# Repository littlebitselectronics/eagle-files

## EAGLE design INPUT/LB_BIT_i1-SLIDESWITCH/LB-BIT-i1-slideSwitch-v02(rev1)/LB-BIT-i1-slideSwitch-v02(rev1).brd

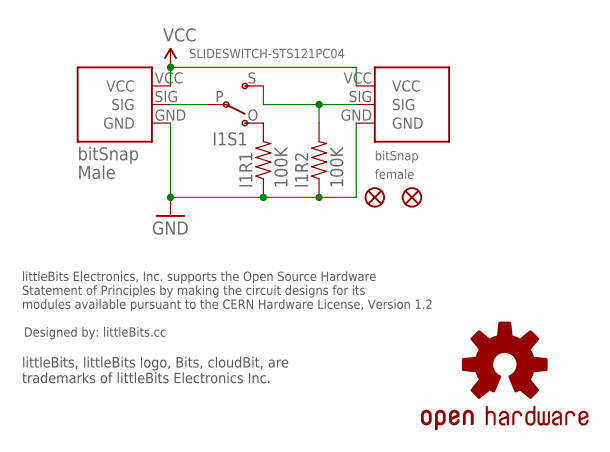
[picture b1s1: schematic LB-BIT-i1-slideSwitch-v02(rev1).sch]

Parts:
I1BSF: BITSNAP_FEMALE
I1BSM: BITSNAP_MALE
I1FD1, I1FD2: FIDUCIAL1X2; FIDUCIAL-1X2
I1R1, I1R2: 100K; 0603-RES
I1S1: SLIDESWITCH-STS121PC04
U$1: OSHWCREDIT
U$2: OSHW-LOGOS; OSHW-LOGO-S

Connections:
GND: I1BSF.GND, I1BSM.GND, I1R1.1, I1R2.1
unnamed: I1BSF.SIG, I1R2.2, I1S1.S
unnamed: I1BSM.SIG, I1S1.P
unnamed: I1R1.2, I1S1.O
VCC: I1BSF.VCC, I1BSM.VCC

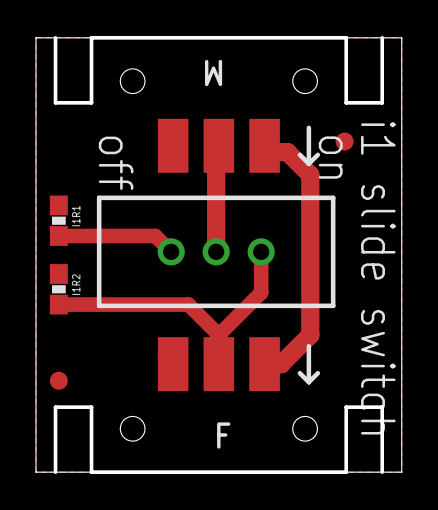
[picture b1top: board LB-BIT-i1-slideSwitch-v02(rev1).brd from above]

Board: 2 copper layers, 20.3 x 24.1 mm, 10 parts (0 on the bottom side), 5 nets.

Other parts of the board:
U$6: OSHW_FILLX150_NOTEXT

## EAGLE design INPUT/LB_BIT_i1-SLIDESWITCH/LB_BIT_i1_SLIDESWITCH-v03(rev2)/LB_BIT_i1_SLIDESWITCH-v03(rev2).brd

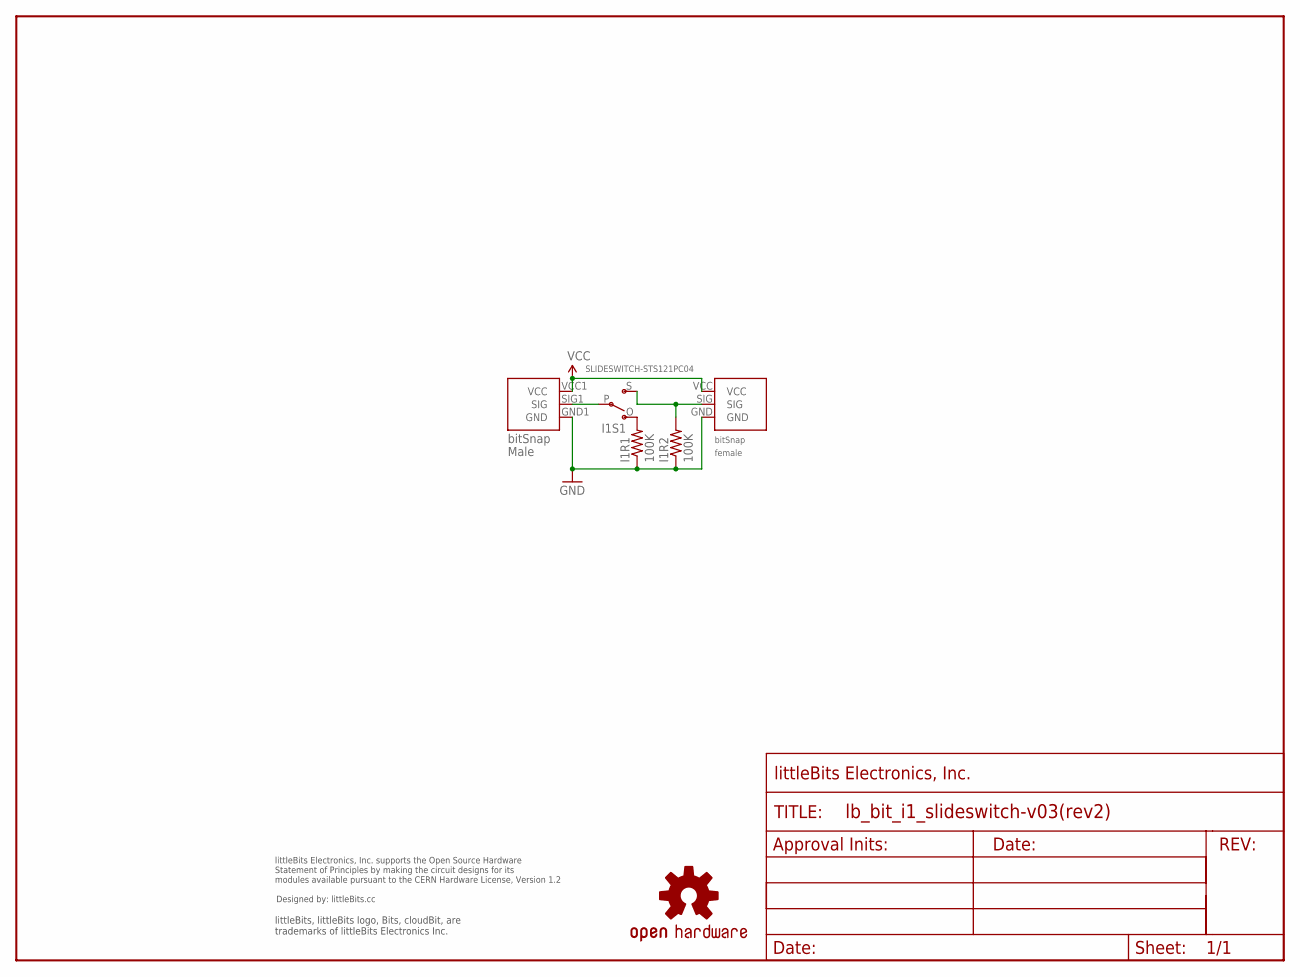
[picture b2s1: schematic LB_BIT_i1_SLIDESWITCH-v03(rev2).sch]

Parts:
I1BSF1: BITSNAP_V03_FEMALE
I1BSM1: BITSNAP_V03_MALE
I1R1, I1R2: 100K; 0603-RES
I1S1: SLIDESWITCH-STS121PC04
U$1: OSHW-LOGOL; OSHW-LOGO-L
U$2: FRAME-LETTER-OHWOHW; FABDWG01-OHW
U$3: LB_CREDITS; OSHWCREDIT

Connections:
GND: I1BSF1.GND, I1BSM1.GND1 (GND), I1R1.1, I1R2.1
unnamed: I1BSF1.SIG, I1R2.2, I1S1.S
unnamed: I1BSM1.SIG1 (SIG), I1S1.P
unnamed: I1R1.2, I1S1.O
VCC: I1BSF1.VCC, I1BSM1.VCC1 (VCC)

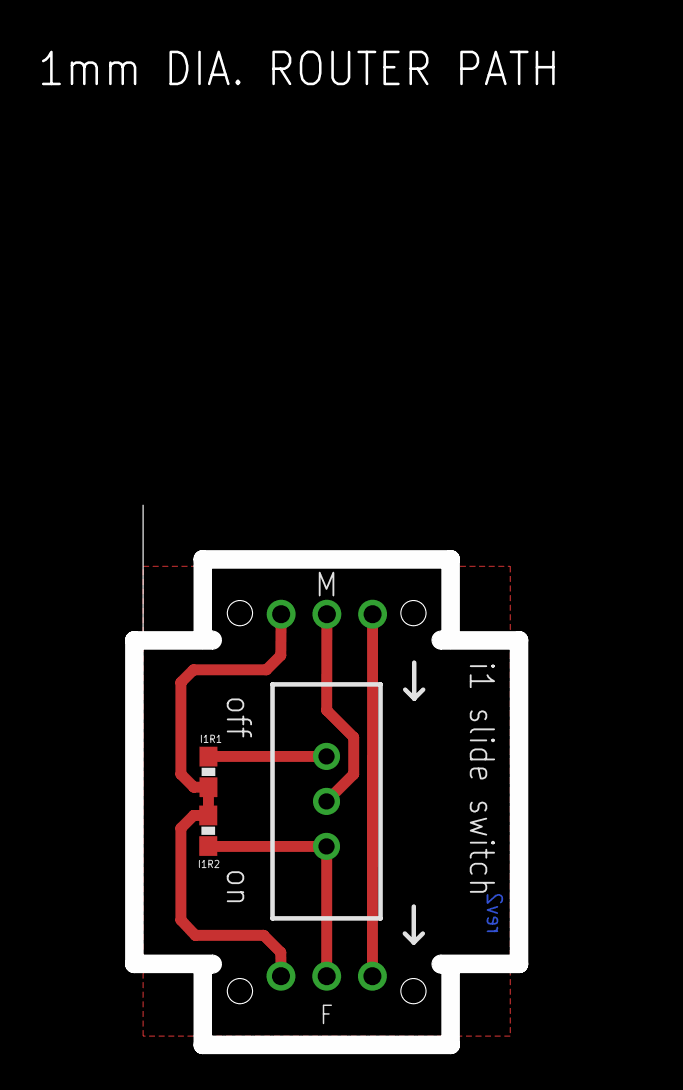
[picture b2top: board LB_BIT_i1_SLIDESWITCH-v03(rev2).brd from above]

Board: 2 copper layers, 21.4 x 27.0 mm, 9 parts (0 on the bottom side), 5 nets.

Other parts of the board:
U$6: OSHW_FILLX150_NOTEXT

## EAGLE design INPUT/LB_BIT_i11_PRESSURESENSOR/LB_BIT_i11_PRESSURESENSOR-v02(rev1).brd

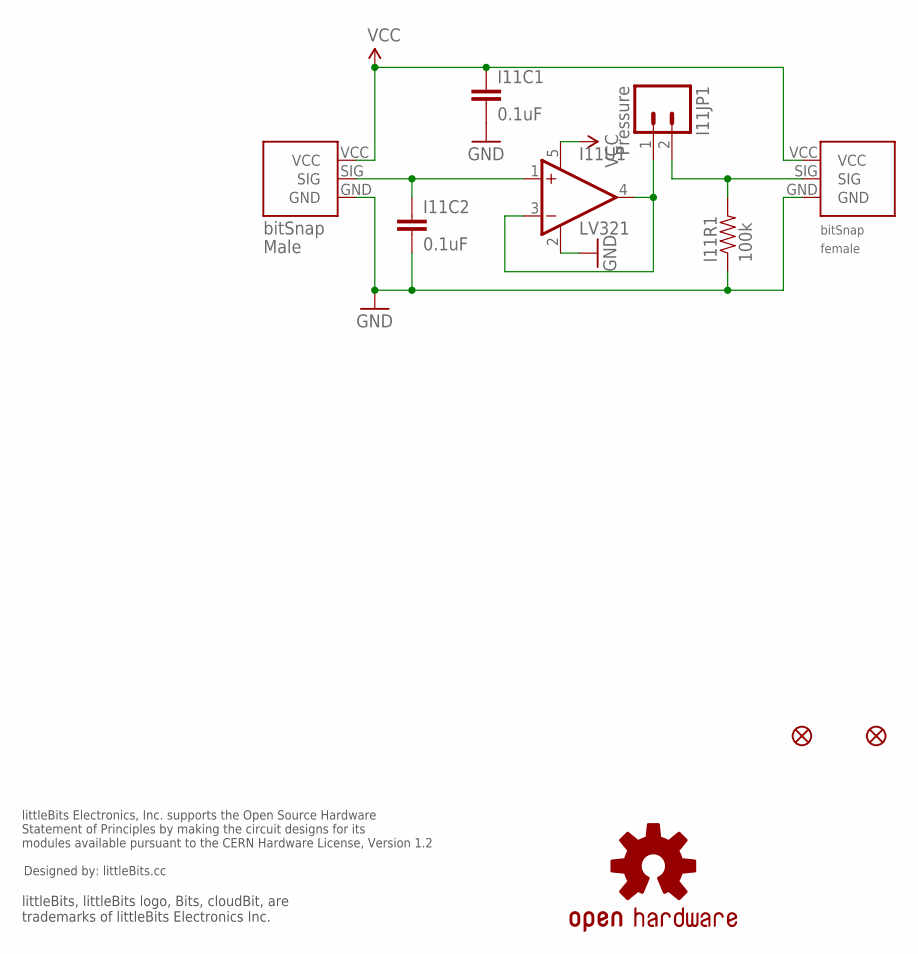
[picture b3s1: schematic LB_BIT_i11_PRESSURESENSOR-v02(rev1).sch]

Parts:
I11BSF: BITSNAP_FEMALE
I11BSM: BITSNAP_MALE
I11C1, I11C2: 0.1uF; 0603-CAP
I11JP1: Pressure; 1X02
I11R1: 100k; 0603-RES
I11U1: LV321; SC70-5
JP2, JP3: FIDUCIAL1X2.5; FIDUCIAL-1X2.5
U$1: OSHWCREDIT
U$4: OSHW-LOGOL; OSHW-LOGO-L

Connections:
GND: I11BSF.GND, I11BSM.GND, I11C1.2, I11C2.2, I11R1.1, I11U1.2 (V-)
unnamed: I11JP1.1, I11U1.3 (-IN), I11U1.4 (OUT)
PS: I11BSF.SIG, I11JP1.2, I11R1.2
SIG: I11BSM.SIG, I11C2.1, I11U1.1 (+IN)
VCC: I11BSF.VCC, I11BSM.VCC, I11C1.1, I11U1.5 (V+)

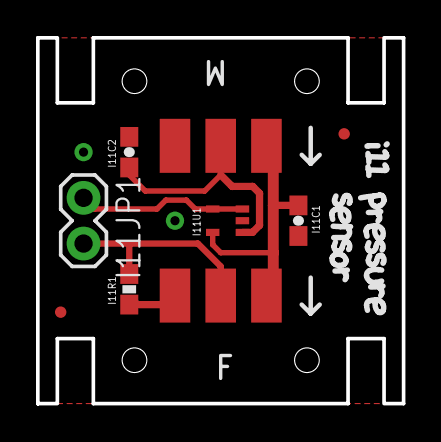
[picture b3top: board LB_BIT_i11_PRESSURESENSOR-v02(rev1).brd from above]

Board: 2 copper layers, 20.3 x 20.3 mm, 12 parts (0 on the bottom side), 5 nets.

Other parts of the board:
U$6: OSHW_FILLX150_NOTEXT

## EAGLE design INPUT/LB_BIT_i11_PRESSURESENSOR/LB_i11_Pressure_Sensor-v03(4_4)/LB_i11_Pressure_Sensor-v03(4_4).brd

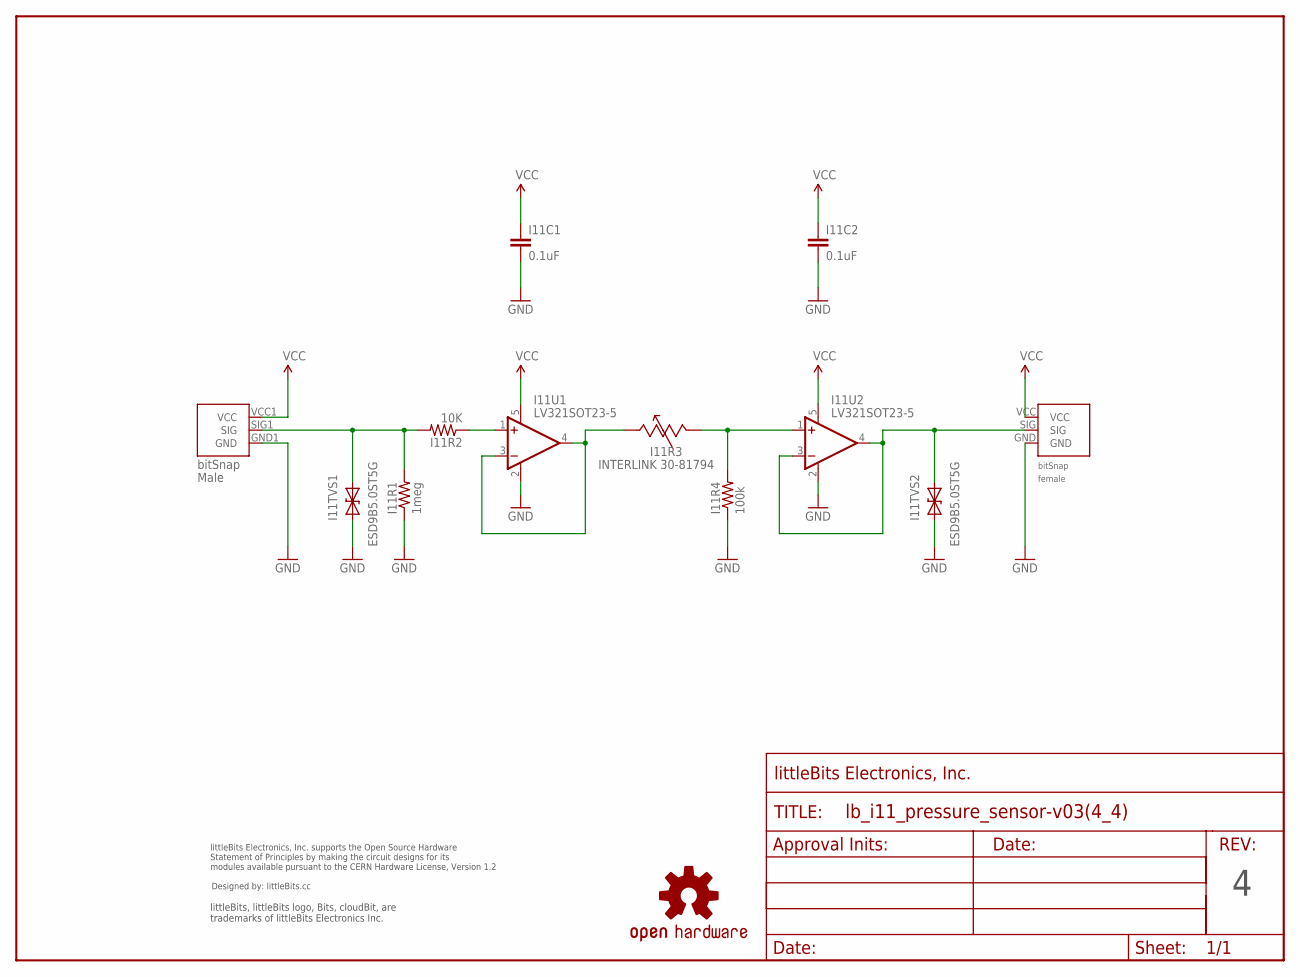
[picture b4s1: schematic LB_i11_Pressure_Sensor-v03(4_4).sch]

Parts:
FRAME1: FRAME-LETTER-OHWOHW; FABDWG01-OHW
I11BSF1: BITSNAP_V03_FEMALE
I11BSM1: BITSNAP_V03_MALE
I11C1, I11C2: 0.1uF; 0603-CAP
I11R1: 1meg; RES-0603
I11R2: 10K; RES-0603
I11R3: INTERLINK 30-81794; FSR-SMD
I11R4: 100k; 0603-RES
I11TVS1, I11TVS2: ESD9B5.0ST5G; SOD-923
I11U1, I11U2: LV321SOT23-5; SOT23-5
U$1: OSHW-LOGOL; OSHW-LOGO-L
U$7: LB_CREDITS; OSHWCREDIT

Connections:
GND: I11BSF1.GND, I11BSM1.GND1 (GND), I11C1.2, I11C2.2, I11R1.1, I11R4.1, I11TVS1.1 (A), I11TVS2.1 (A), I11U1.2 (V-), I11U2.2 (V-)
unnamed: I11R3.2 (A), I11R4.2, I11U2.1 (+IN)
unnamed: I11BSF1.SIG, I11TVS2.2 (C), I11U2.3 (-IN), I11U2.4 (OUT)
unnamed: I11R3.1, I11U1.3 (-IN), I11U1.4 (OUT)
unnamed: I11R2.1, I11U1.1 (+IN)
SIG2: I11BSM1.SIG1 (SIG), I11R1.2, I11R2.2, I11TVS1.2 (C)
VCC: I11BSF1.VCC, I11BSM1.VCC1 (VCC), I11C1.1, I11C2.1, I11U1.5 (V+), I11U2.5 (V+)

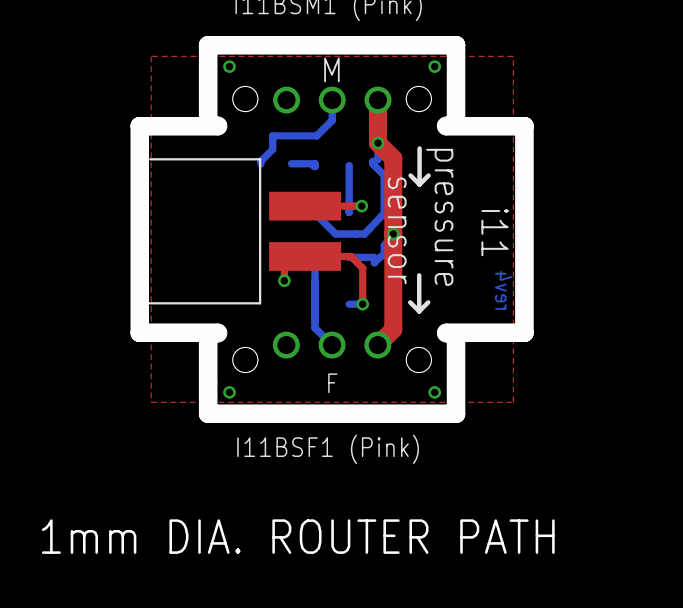
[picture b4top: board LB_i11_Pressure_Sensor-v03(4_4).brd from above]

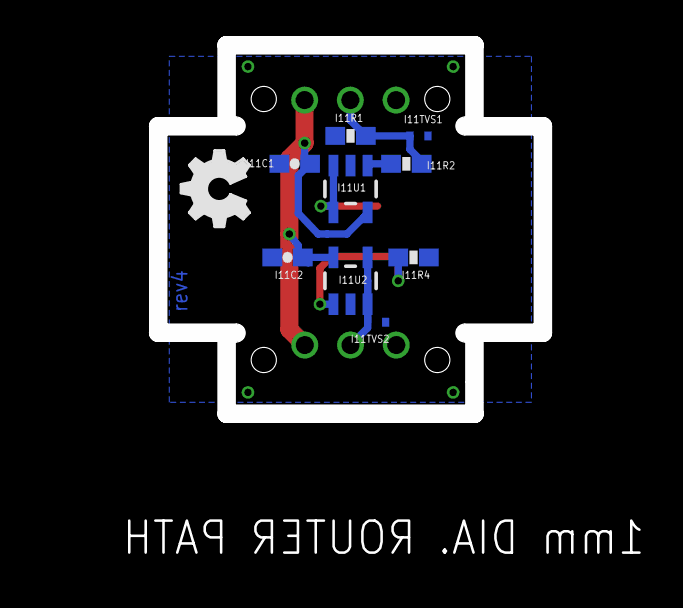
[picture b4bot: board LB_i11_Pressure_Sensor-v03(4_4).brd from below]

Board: 2 copper layers, 21.4 x 20.5 mm, 16 parts (9 on the bottom side), 7 nets.

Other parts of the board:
U$6: OSHW_FILLX150_NOTEXT

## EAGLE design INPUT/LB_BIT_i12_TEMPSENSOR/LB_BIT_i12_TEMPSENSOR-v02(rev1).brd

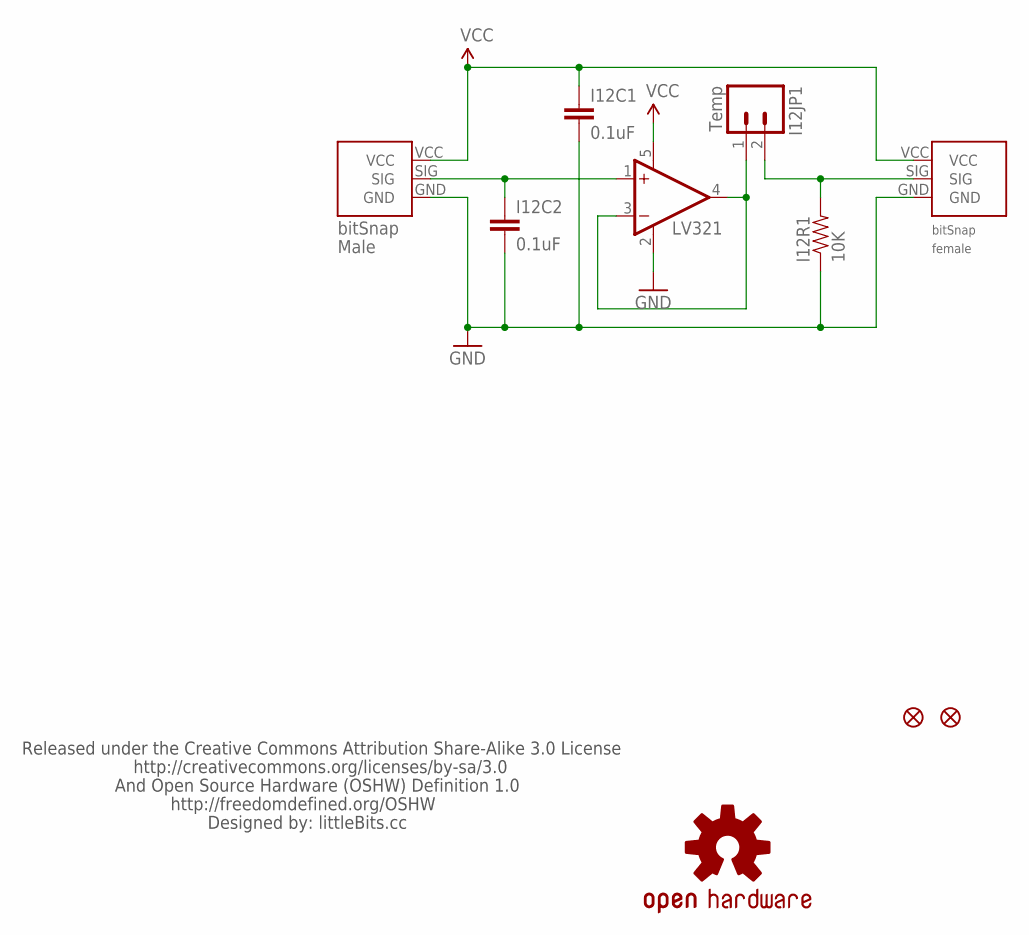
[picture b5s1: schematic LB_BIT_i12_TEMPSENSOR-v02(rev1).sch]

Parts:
I12BSF: BITSNAP_FEMALE
I12BSM: BITSNAP_MALE
I12C1, I12C2: 0.1uF; 0603-CAP
I12JP1: Temp; 1X02
I12R1: 10K; 0603-RES
I12U1: LV321; SC70
JP2, JP3: FIDUCIAL1X2; FIDUCIAL-1X2
U$1: OSHW-LOGOL; OSHW-LOGO-L
U$18: LB_CREDITS_V2

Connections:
GND: I12BSF.GND, I12BSM.GND, I12C1.2, I12C2.2, I12R1.1, I12U1.2 (V-)
unnamed: I12JP1.1, I12U1.3 (-IN), I12U1.4 (OUT)
PS: I12BSF.SIG, I12JP1.2, I12R1.2
SIG: I12BSM.SIG, I12C2.1, I12U1.1 (+IN)
VCC: I12BSF.VCC, I12BSM.VCC, I12C1.1, I12U1.5 (V+)

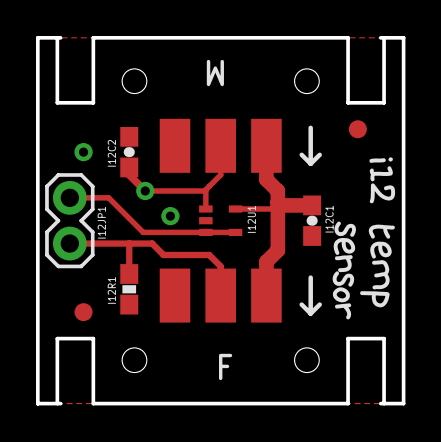
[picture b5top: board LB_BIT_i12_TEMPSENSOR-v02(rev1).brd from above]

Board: 2 copper layers, 20.3 x 20.3 mm, 25 parts (0 on the bottom side), 5 nets.

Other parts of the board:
U$2: I
U$3: 1
U$6: OSHW_FILLX150_NOTEXT
U$7: 2
U$8: T
U$9, U$13: E
U$10: M
U$11: P
U$12, U$15: S
U$14: N
U$16: O
U$17: R

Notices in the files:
parts and their libraries:
LITTLEBITS: modules available pursuant to the CERN Hardware License,
Version 1.2
LITTLEBITS: modules available pursuant to the CERN Hardware License, Version 1.2
LITTLEBITS: Released under the Creative Commons Attribution Share-Alike 3.0 License
